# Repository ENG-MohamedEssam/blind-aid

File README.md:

# blind-aid

## Abstract 

#### This project was mainly split into two parts, the first one is using machine learning to identify 80 different objects and the code was working properly on the laptop and for future intentions i was going to move it to work on raspberry pi.
#### The second part was using small microcontroller to make the device cheaper and easy to aquire by many people, this part was meant to replace the stick that the blind would use by a small ring to wear in your hand.

## What are the components of the ring ?
#### mainly it has it's controller which is Atmega328p, A small potentiometer, a dip switch, a vibration motor like the ones in the mobile phones, and a laser sensor (VL53L0X Time of Flight Sensor) which has up to 2m percison distance

## How does the ring work?

#### The ring turns on/off using a switch when you point it to a rigid object it gives a sense of vibration to your hand and when you get closer to the object the ring vibrates even more and that gives you the sense of how close the object is to your hand.
### Note that  #### You can adjust the sensetivity of the device using the small potentiometer that's on the ring

#### I designed the ring on SolidWorks as you can see below

#### The board should take the top of the ring as it's housing and the bottom of the ring is meant for the laser sensor
#### I 3D-printed the ring as you can see below

#### And the follwing is the design of the board

#### The ring worked perfectly on a breadboard and for future intentions the board will be made and the product will be finished soon.

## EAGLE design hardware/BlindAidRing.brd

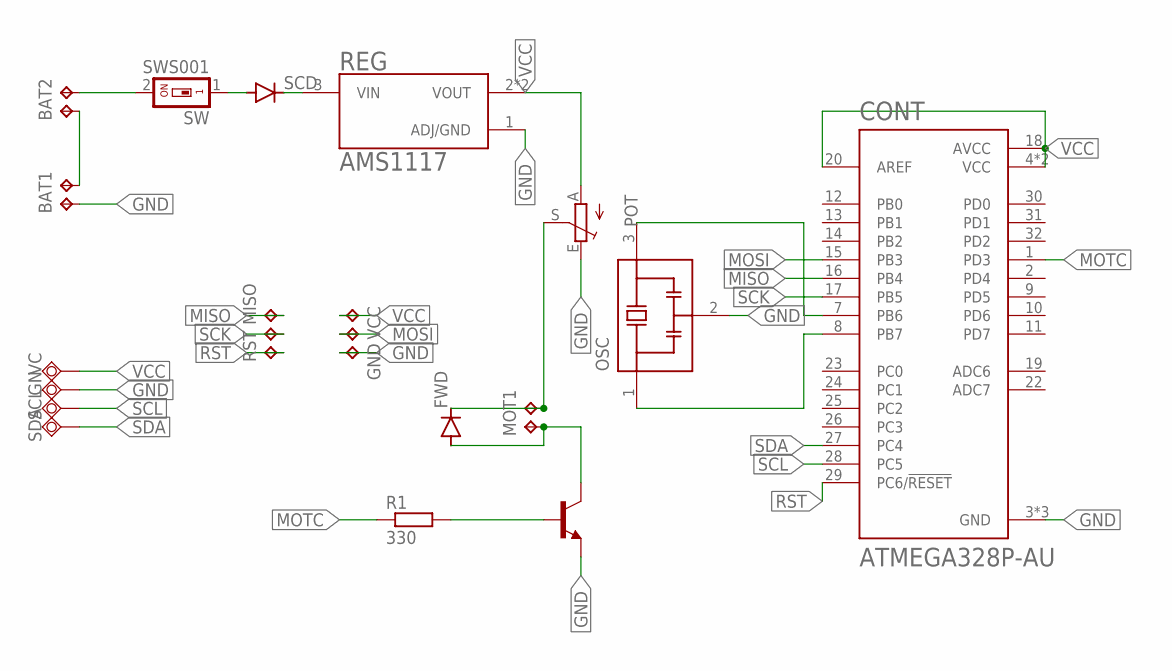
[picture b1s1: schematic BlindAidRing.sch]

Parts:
BAT1, BAT2, BAT11, BAT22: TPTP20SQ; TP20SQ
CONT: ATMEGA328P-AU; QFP80P900X900X120-32N
FWD: CGRM4002-G; SOD-123_MINI-SMA
GN: TPSQTP18SQ; TP18SQ
GND: TPB1,27; B1,27
MISO: TPB1,27; B1,27
MOSI: TPB1,27; B1,27
MOT1, MOT2: TPTP20SQ; TP20SQ
OSC: CSTCE16M0V53-R0; OSC_CSTCE16M0V53-R0
POT: TRIM_EU-CA6V; CA6V
R1: 330; R0603
REG: AMS1117; SOT229P700X180-4N
RST: TPB1,27; B1,27
SCD: CGRM4002-G; SOD-123_MINI-SMA
SCK: TPB1,27; B1,27
SCL: TPSQTP18SQ; TP18SQ
SDA: TPSQTP18SQ; TP18SQ
SW: SWS001; SMS-001
T1: -NPN-SOT23-EBC; SOT23-EBC
VC: TPSQTP18SQ; TP18SQ
VCC: TPB1,27; B1,27

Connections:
GND: BAT1.TP, CONT.3 (GND), CONT.5 (GND), CONT.21 (GND), GN.TP, GND.TP, OSC.2 (GND), POT.E, REG.1 (ADJ/GND), T1.E
MISO: CONT.16 (PB4), MISO.TP
MOSI: CONT.15 (PB3), MOSI.TP
MOTC: CONT.1 (PD3), R1.1
unnamed: FWD.C, MOT2.TP, POT.S
unnamed: FWD.A, MOT1.TP, T1.C
unnamed: BAT22.TP, SW.2
unnamed: R1.2, T1.B
unnamed: BAT2.TP, BAT11.TP
unnamed: REG.3 (VIN), SCD.C
unnamed: SCD.A, SW.1
unnamed: CONT.7 (PB6), OSC.3 (OUT)
unnamed: CONT.8 (PB7), OSC.1 (IN)
RST: CONT.29 (PC6/!RESET), RST.TP
SCK: CONT.17 (PB5), SCK.TP
SCL: CONT.28 (PC5), SCL.TP
SDA: CONT.27 (PC4), SDA.TP
VCC: CONT.4 (VCC), CONT.6 (VCC), CONT.18 (AVCC), CONT.20 (AREF), POT.A, REG.2 (VOUT), REG.4 (VOUT), VC.TP, VCC.TP

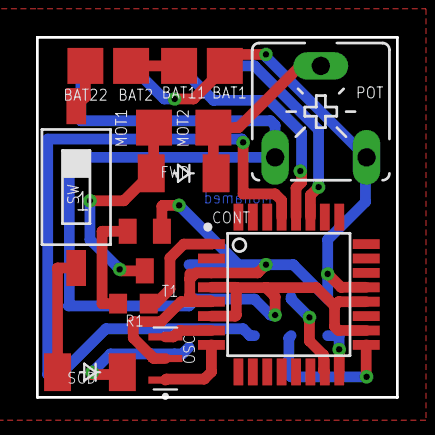
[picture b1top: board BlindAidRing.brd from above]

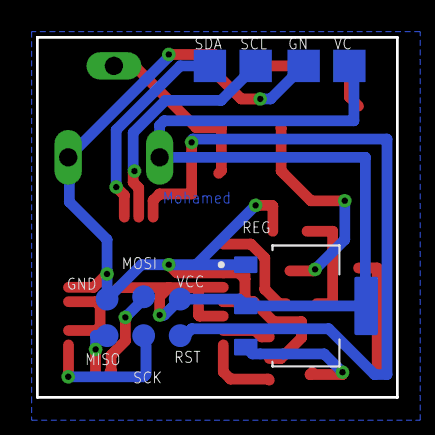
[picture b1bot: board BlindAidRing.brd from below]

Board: 2 copper layers, 20.0 x 20.0 mm, 25 parts (11 on the bottom side), 18 nets.

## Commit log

2022-12-09 Addig images
2022-12-09 Edit readme
